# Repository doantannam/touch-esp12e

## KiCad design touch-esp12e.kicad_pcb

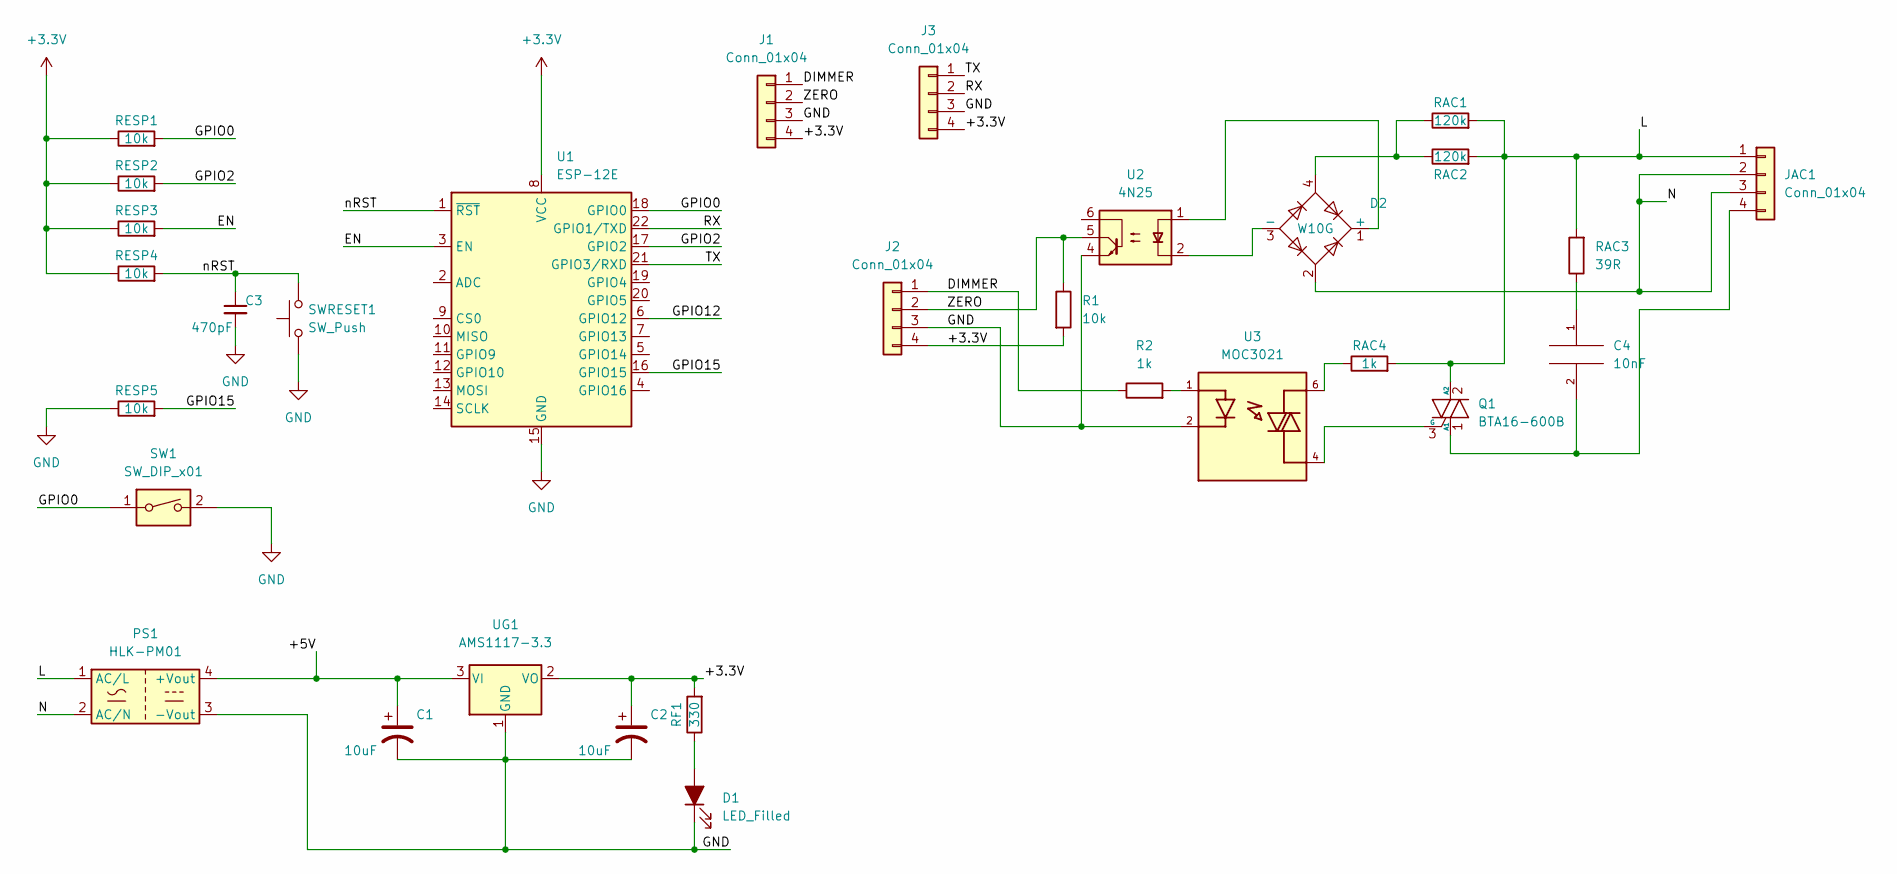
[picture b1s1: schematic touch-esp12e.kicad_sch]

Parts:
C1, C2: 10uF; CP_Radial_D5.0mm_P2.50mm
C3: 470pF; C_Disc_D5.0mm_W2.5mm_P5.00mm
C4: 10nF; C_Disc_D10.5mm_W5.0mm_P10.00mm
D1: LED_Filled; LED_D3.0mm
D2: W10G; Diode_Bridge_Round_D9.8mm
J1, J3: Conn_01x04; PinHeader_1x04_P2.54mm_Vertical
J2: Conn_01x04; PinSocket_1x04_P2.54mm_Vertical
JAC1: Conn_01x04; SolderWire-2sqmm_1x04_P7.8mm_D2mm_OD3.9mm
PS1: HLK-PM01; Converter_ACDC_HiLink_HLK-PMxx
Q1: BTA16-600B; TO-220-3_Vertical
R1: 10k; R_Axial_DIN0207_L6.3mm_D2.5mm_P7.62mm_Horizontal
R2: 1k; R_Axial_DIN0414_L11.9mm_D4.5mm_P15.24mm_Horizontal
RAC1, RAC2: 120k; R_Axial_DIN0414_L11.9mm_D4.5mm_P15.24mm_Horizontal
RAC3: 39R; R_Axial_DIN0414_L11.9mm_D4.5mm_P15.24mm_Horizontal
RAC4: 1k; R_Axial_DIN0414_L11.9mm_D4.5mm_P15.24mm_Horizontal
RESP1, RESP2, RESP3, RESP4, RESP5: 10k; R_Axial_DIN0207_L6.3mm_D2.5mm_P7.62mm_Horizontal
RF1: 330; R_Axial_DIN0207_L6.3mm_D2.5mm_P7.62mm_Horizontal
SW1: SW_DIP_x01; SW_DIP_SPSTx01_Slide_9.78x4.72mm_W7.62mm_P2.54mm
SWRESET1: SW_Push; SW_PUSH_6mm
U1: ESP-12E
U2: 4N25; DIP-6_W7.62mm
U3: MOC3021; DIP762W45P254L889H508Q6
UG1: AMS1117-3.3; SOT-223-3_TabPin2

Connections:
+3.3V: C2.1, J1.4, J2.4, J3.4, R1.2, RESP1.1, RESP2.1, RESP3.1, RESP4.1, RF1.2, U1.8 (VCC), UG1.2 (VO)
/+5V: C1.1, PS1.4 (+Vout), UG1.3 (VI)
/DIMMER: J1.1, J2.1, R2.1
/EN: RESP3.2, U1.3 (EN)
/GPIO0: RESP1.2, SW1.1, U1.18 (GPIO0)
/GPIO2: RESP2.2, U1.17 (GPIO2)
/GPIO12: U1.6 (GPIO12)
/GPIO15: RESP5.2, U1.16 (GPIO15)
/L: JAC1.1, PS1.1 (AC/L), Q1.2 (A2), RAC1.2, RAC2.2, RAC3.2, RAC4.2
/N: D2.2, JAC1.2, JAC1.3, PS1.2 (AC/N)
/RX: J3.2, U1.22 (GPIO1/TXD)
/TX: J3.1, U1.21 (GPIO3/RXD)
/ZERO: J1.2, J2.2, R1.1, U2.5
/nRST: C3.1, RESP4.2, SWRESET1.1, U1.1 (~RST)
GND: C1.2, C2.2, C3.2, D1.1 (K), J1.3, J2.3, J3.3, PS1.3 (-Vout), RESP5.1, SW1.2, SWRESET1.2, U1.15 (GND), U2.4, U3.2, UG1.1 (GND)
unnamed: C4.1, RAC3.1
unnamed: C4.2, JAC1.4, Q1.1 (A1)
unnamed: D1.2 (A), RF1.1
unnamed: D2.1 (+), U2.1
unnamed: D2.3 (-), U2.2
unnamed: D2.4, RAC1.1, RAC2.1
unnamed: Q1.3 (G), U3.4
unnamed: R2.2, U3.1
unnamed: RAC4.1, U3.6

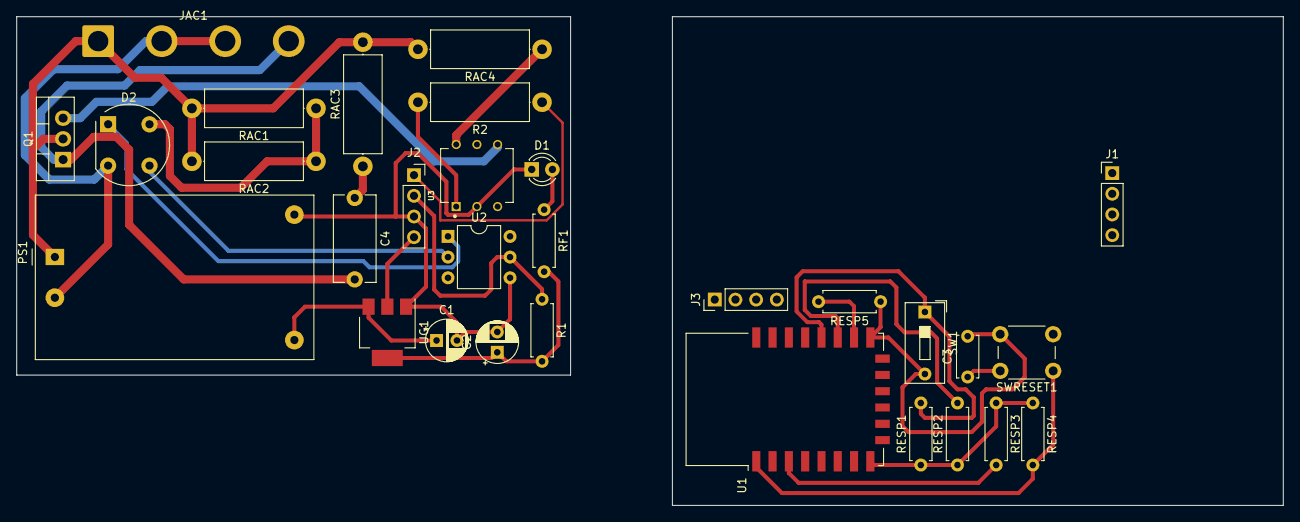
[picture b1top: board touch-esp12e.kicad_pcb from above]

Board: 2 copper layers, 155.5 x 60.0 mm, 30 parts (0 on the bottom side), 23 nets.

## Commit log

2022-12-25 create touch
2022-12-26 new-touch
